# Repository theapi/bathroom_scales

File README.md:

# Bathroom Scales
Hacked bathroom scales to provide data logging

See https://learn.sparkfun.com/tutorials/load-cell-amplifier-hx711-breakout-hookup-guide

Sparkfun repo: https://github.com/sparkfun/HX711-Load-Cell-Amplifier

Library: https://github.com/bogde/HX711

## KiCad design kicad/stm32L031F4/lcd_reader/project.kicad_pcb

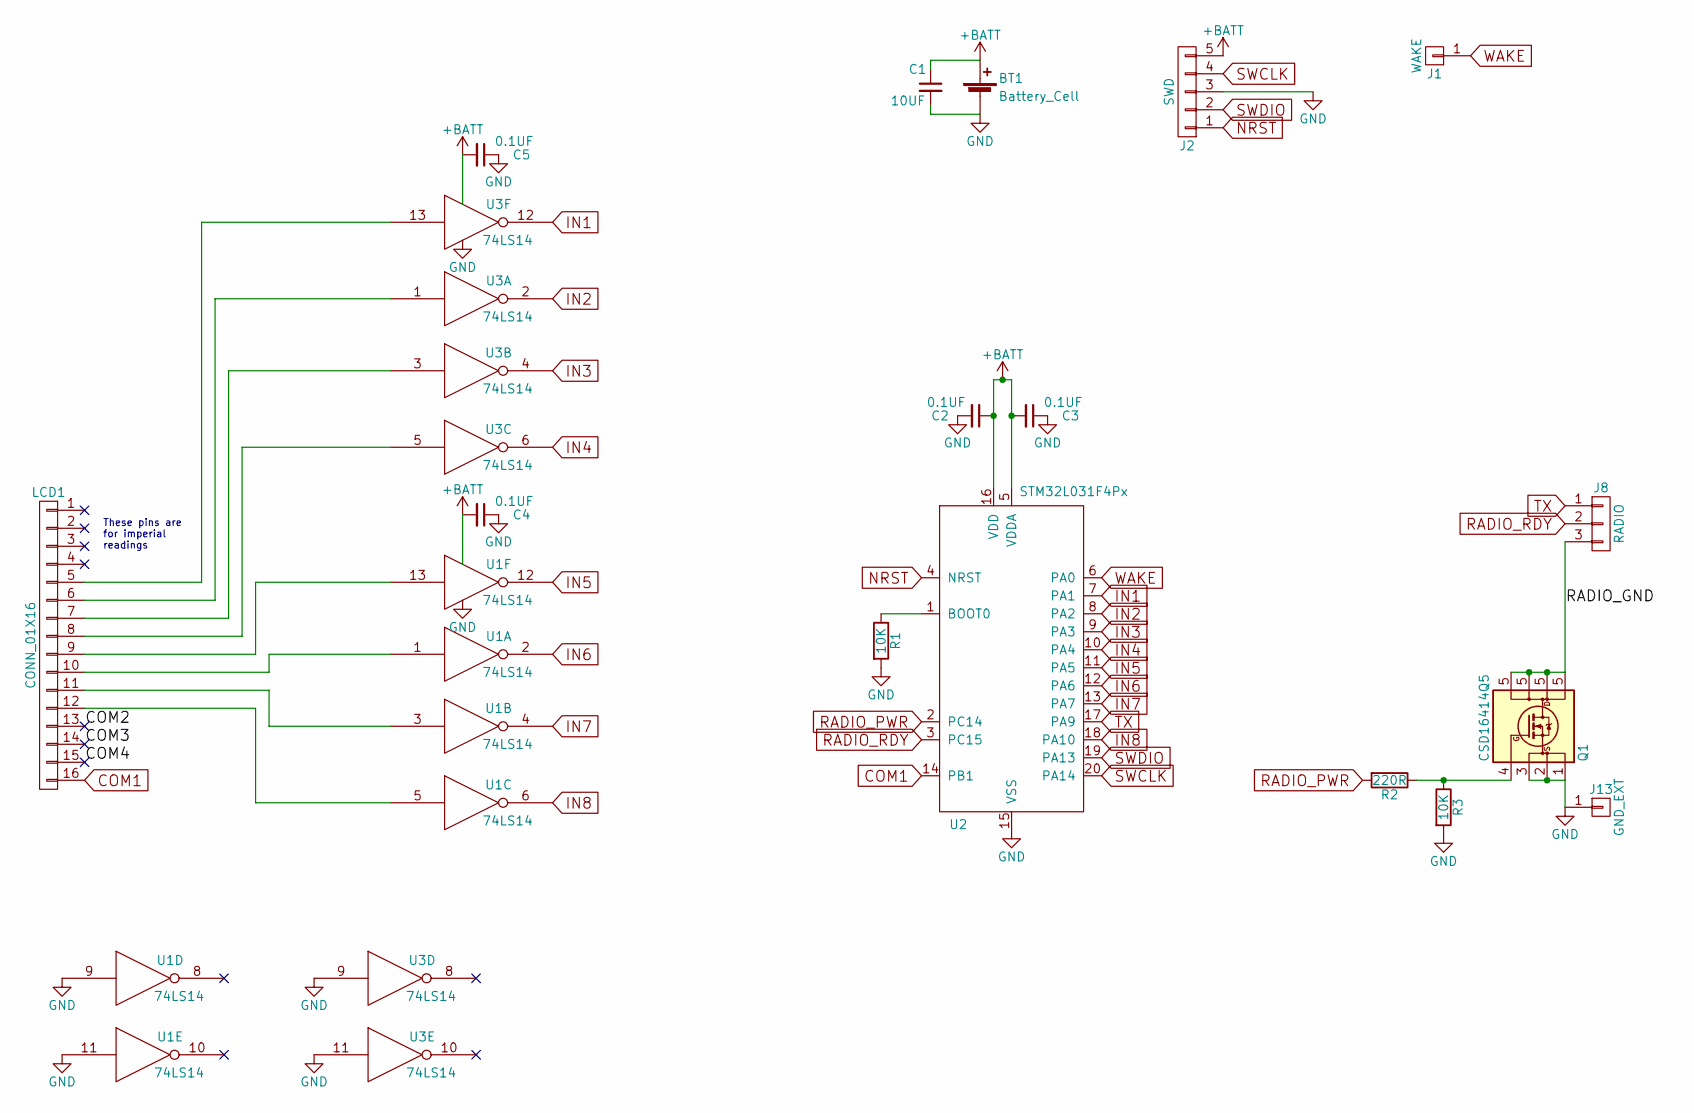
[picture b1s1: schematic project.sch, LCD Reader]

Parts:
BT1: Battery_Cell; Pin_Header_Straight_2x01_Pitch2.54mm
C1: 10UF; C_0805_HandSoldering
C2, C3, C4, C5: 0.1UF; C_0805_HandSoldering
J1: WAKE; Pin_Header_Straight_1x01_Pitch2.54mm
J2: SWD; Pin_Header_Straight_1x05_Pitch2.54mm
J8: RADIO; Pin_Header_Straight_1x03_Pitch2.54mm
J13: GND_EXT; Pin_Header_Straight_1x01_Pitch2.54mm
LCD1: CONN_01X16; ZEBRA-16
Q1: CSD16414Q5; TDSON-8-1_HandSoldering
R1, R3: 10K; R_0805_HandSoldering
R2: 220R; R_0805_HandSoldering
U1, U3: 74LS14; SOIC-14_3.9x8.7mm_Pitch1.27mm
U2: STM32L031F4Px; TSSOP-20_4.4x6.5mm_Pitch0.65mm

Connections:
+BATT: BT1.1 (+), C1.1, C2.1, C3.2, C4.2, C5.2, J2.5, U1.14 (VCC), U2.5 (VDDA), U2.16 (VDD), U3.14 (VCC)
/COM2: LCD1.13
/COM3: LCD1.14
/COM4: LCD1.15
/RADIO_GND: J8.3, Q1.5 (D)
COM1: LCD1.16, U2.14 (PB1)
GND: BT1.2 (-), C1.2, C2.2, C3.1, C4.1, C5.1, J2.3, J13.1, Q1.1 (S), Q1.2 (S), Q1.3 (S), R1.2, R3.2, U1.7 (GND), U1.9, U1.11, U2.15 (VSS), U3.7 (GND), U3.9, U3.11
IN1: U2.7 (PA1), U3.12
IN2: U2.8 (PA2), U3.2
IN3: U2.9 (PA3), U3.4
IN4: U2.10 (PA4), U3.6
IN5: U1.12, U2.11 (PA5)
IN6: U1.2, U2.12 (PA6)
IN7: U1.4, U2.13 (PA7)
IN8: U1.6, U2.18 (PA10)
NRST: J2.1, U2.4 (NRST)
unnamed: LCD1.5, U3.13
unnamed: LCD1.6, U3.1
unnamed: LCD1.7, U3.3
unnamed: LCD1.8, U3.5
unnamed: LCD1.9, U1.13
unnamed: LCD1.10, U1.1
unnamed: LCD1.11, U1.3
unnamed: LCD1.12, U1.5
unnamed: Q1.4 (G), R2.1, R3.1
unnamed: R1.1, U2.1 (BOOT0)
RADIO_PWR: R2.2, U2.2 (PC14)
RADIO_RDY: J8.2, U2.3 (PC15)
SWCLK: J2.4, U2.20 (PA14)
SWDIO: J2.2, U2.19 (PA13)
TX: J8.1, U2.17 (PA9)
WAKE: J1.1, U2.6 (PA0)

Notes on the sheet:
These pins are for imperial readings

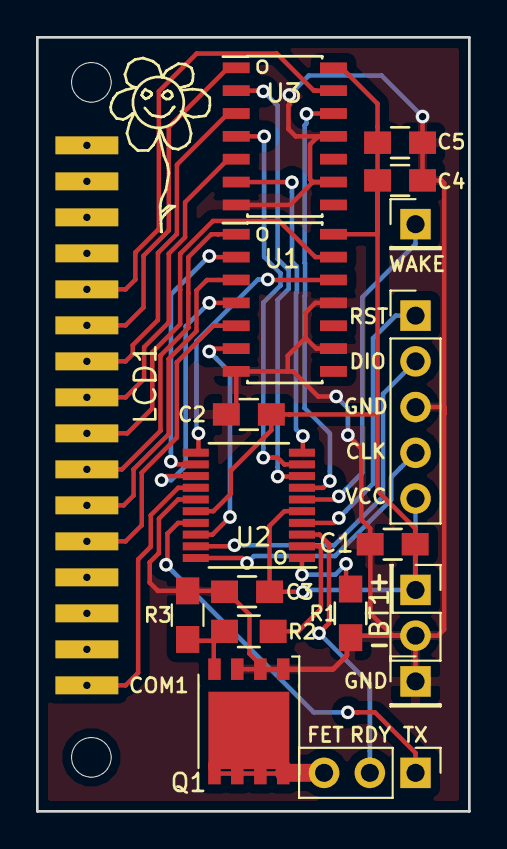
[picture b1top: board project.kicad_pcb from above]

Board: 2 copper layers, 24.0 x 43.0 mm, 18 parts (0 on the bottom side), 29 nets.

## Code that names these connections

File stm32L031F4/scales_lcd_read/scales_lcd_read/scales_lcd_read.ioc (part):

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Mcu.Name=STM32L031F(4-6)Px
Mcu.Package=TSSOP20
Mcu.UserName=STM32L031F4Px
PA0-CK_IN.Mode=SYS_WakeUp0
PA0-CK_IN.Signal=SYS_WKUP1
PA1.Signal=GPIO_Input
PA10.Signal=GPIO_Input
PA13.Mode=Serial_Wire
PA13.Signal=SYS_SWDIO
PA14.Mode=Serial_Wire
PA14.Signal=SYS_SWCLK
PA2.Signal=GPIO_Input
PA3.Signal=GPIO_Input
PA4.Signal=GPIO_Input
PA5.Signal=GPIO_Input
PA6.Signal=GPIO_Input
PA7.Signal=GPIO_Input
PA9.Mode=Half_duplex(single_wire_mode)
PA9.Signal=USART2_TX
PB1.Mode=IN9
PB1.Signal=ADC_IN9
PC14-OSC32_IN.Signal=GPIO_Output
PC15-OSC32_OUT.GPIOParameters=GPIO_PuPd
PC15-OSC32_OUT.GPIO_PuPd=GPIO_PULLUP
PC15-OSC32_OUT.Signal=GPIO_Input
RCC.HSE_VALUE=8000000
RCC.SYSCLKFreq_VALUE=1048000
board=scales_lcd_read

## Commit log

2017-08-29 HX711 library
2017-08-29 HX711 ca;ibration
2017-09-29 Data logger
2017-09-29 Config class
2017-09-29 Figure out which sheet to use by the weight of the person
2017-09-29 Use the composer autoloader
2017-09-29 settings.php instead of config.php
2017-09-30 Multiple inputs & outputs
2017-09-30 Full paths in settings.php
2017-09-30 Cli input
2017-10-03 CSV output
2017-10-04 Basic http client
2017-10-04 Deep sleep between get requests
2017-10-04 Wifi credentials
2017-10-05 Start of schematic
2017-10-05 AnalogRead()
2017-10-05 Wake up is simply rising edge
2017-10-06 ESP32 WROOM
2017-10-06 Schematic
2017-10-07 Start of data class
2017-10-07 Data row class
2017-10-07 Battery voltage
2017-10-09 One place for validation
2017-10-09 Send battery reading
2017-10-10 Simpler
2017-10-10 Value variables
2017-10-10 Simpler config
2017-10-10 Changed battery pin to one that supports ADC1
2017-10-11 Restructured the layout
2017-10-11 Esp32 specific
2017-10-11 Moved dir
2017-10-12 Adafruit feather
2017-10-17 Updated namespaces
2017-10-22 HX711 expriments with arduino nano
2017-10-28 External wakeup
2017-10-28 Use pin 34 (A2 on Adafruit feather) for wake up
2017-10-28 Check pin 34 status
2017-10-29 Start of reading the LCD screen
2017-10-29 Use COM0 as the start frame indicator
2017-10-29 Decode segments
2017-10-29 Two digits
2017-10-29 Only serial print the reading
2017-10-29 Third digit
2017-10-29 Fourth digit
2017-10-29 Schmitt trigger & ESP32 Feather pinout
2017-11-04 Fails to read due to wifi hogginf resources
2017-11-04 Start of reading the lcd with an stm32L031F4
2017-11-04 Read the pins
2017-11-04 Slower programming
2017-11-04 Also show the direct read of the pins
2017-11-05 Lower clock speed & vcore
2017-11-05 Enter standby mode
2017-11-05 Disable the uart after transmission
2017-11-05 HAL reconfigures the pin input
2017-11-05 standby()
2017-11-05 Lower power voltage scale
2017-11-05 Only send serial data if PC15 is high
2017-11-05 Start of esp32 just for thewifi
2017-11-06 stm32L031F4 board
2017-11-06 All connected
2017-11-07 Labels
2017-11-07 Logos
2017-11-07 Silkscreen tidying
2017-11-07 gerbers
2017-11-08 Start of zebra strip compatability
2017-11-08 Layout for sandwiched zebra connector
2017-11-09 Main zebra connection on the top
2017-11-09 SOIC-14 for the schmitt triggers
2017-11-09 Datasheets
2017-11-20 Start of lcd read
2017-11-20 LCD_getPinValues()
2017-11-20 Send the weight to the esp32
2017-11-21 Moved to experimental
2017-11-21 Transmit in grams to avoid floats
2017-11-21 Send the values to the server
2017-11-21 Communication between esp32 & STM32
2017-11-21 Crude power control of the transmitter
2017-11-21 Flacky communications
2017-11-21 Transfer weight as binary in the serial transmission
2017-11-21 Read the serial data in a state machine
2017-11-21 Fighting theesp hanging
2017-11-21 esp8266
2017-11-22 Deep sleep the esp
2017-11-22 Once a minute
2017-11-22 Sleep with no wake until power cycle
2017-11-30 Start of tx state machine
2017-12-04 Start of scales state machine
2017-12-05 LCD_read()
2017-12-05 Start of running the readings in a state machine
2017-12-07 Digit decode
2017-12-13 LCD_run()
2017-12-14 Hard wired fake transmitter for initial hardware test
2017-12-19 Pull down on mosfet gate
2017-12-19 Transmitter control
2017-12-19 Transmitter states
2017-12-19 2 space formatting
2017-12-19 Read only, for testing lcd read values
2017-12-21 Read values
2017-12-21 Works reading the real screen
2017-12-21 Merged lcd work from read_only branch
2017-12-21 Use LCD_pollForWeight()
